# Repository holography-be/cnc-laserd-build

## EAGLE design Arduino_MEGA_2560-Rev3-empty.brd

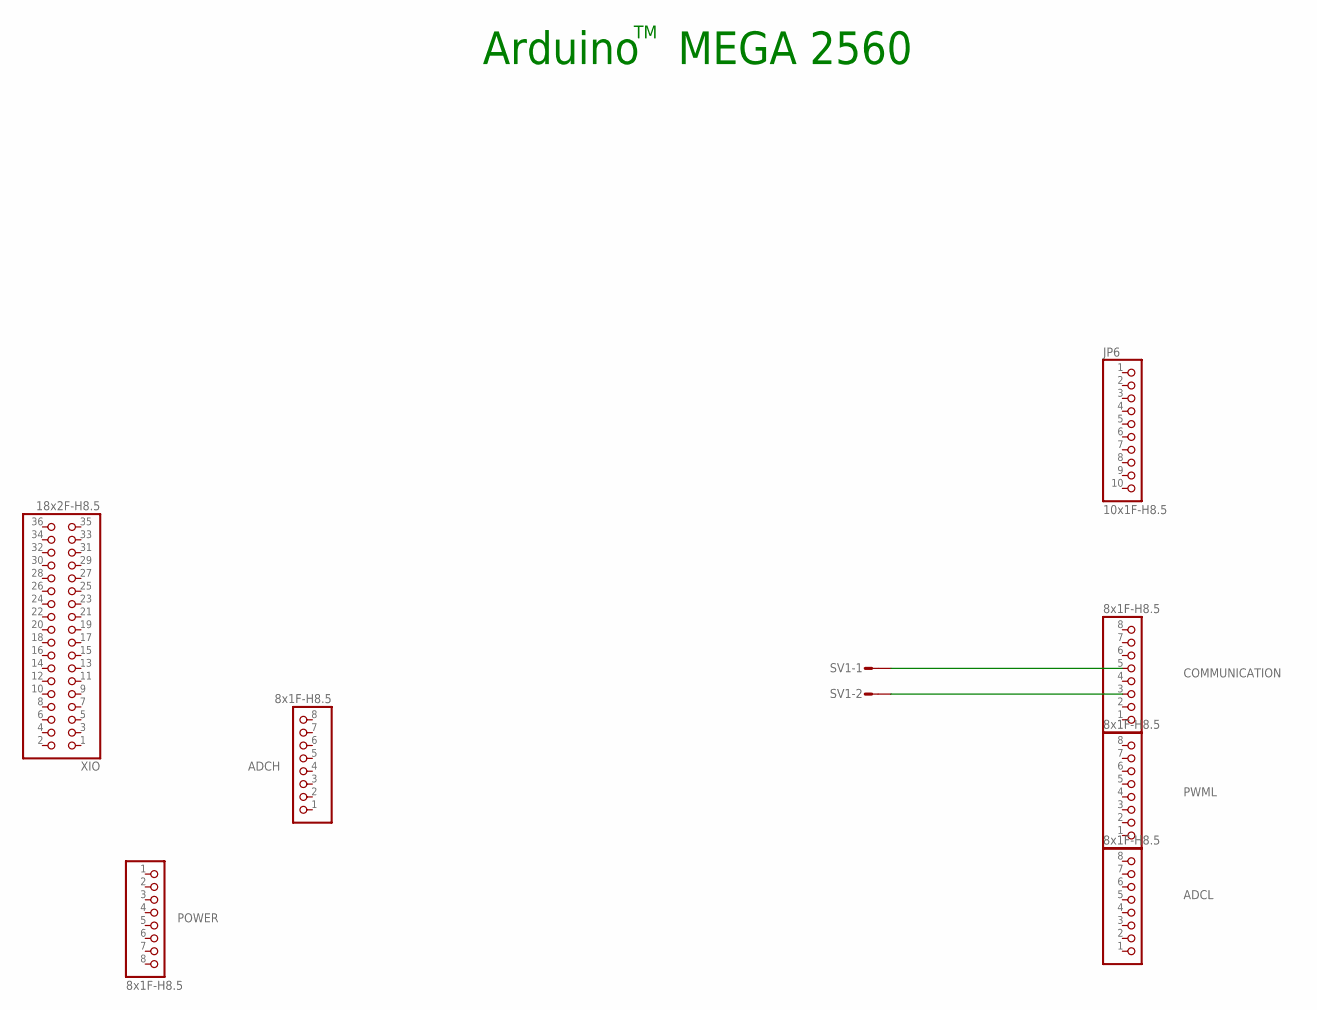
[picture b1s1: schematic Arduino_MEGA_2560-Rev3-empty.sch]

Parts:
ADCH: 8x1F-H8.5; 1X08
ADCL: 8x1F-H8.5; 1X08
COMMUNICATION: 8x1F-H8.5; 1X08
JP6: 10x1F-H8.5; 1X10
POWER: 8x1F-H8.5; 1X08
PWML: 8x1F-H8.5; 1X08
SV1: S02P
XIO: 18x2F-H8.5; 2X18

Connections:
unnamed: COMMUNICATION.5, SV1.1
unnamed: COMMUNICATION.3, SV1.2

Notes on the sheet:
Arduino MEGA 2560

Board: 2 copper layers, 8 parts (0 on the bottom side), 2 nets, no tracks yet.

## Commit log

2016-02-07 Create MotorShield
